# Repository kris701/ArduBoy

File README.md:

# ArduBoy

This is a project to make my own gameboy-like console, with its own scripting language and dynamic runtime on an Arduino.

Physically, its more or less equal to a Gameboy Pocket, except this one is a bit thicker and the screen is a bit smaller.
Other than that, it has the same button layout. 
Instead of using disposable batteries, it has a internal LiPo instead with a USB-C port for charging.
Games are semi-compiled into a easier to read format for the Arduino. The semi-compiled code is put on an SD card, that the ArduBoy can then parse and run.

In hindsight, it might have a bit of an overkill battery of 3000mAh, so it can technically run for a few days without a charge.

You can take a look in the [Games](./Games) folder for some already made games for the Arduino, or you can make some yourself!

You can use the CLI tool to compile the script file onto an SD card.
The tool will also do a bit of syntax checking to make sure there arent obvious errors in the script file.

## ArduBoy Script (`.abs`) Syntax

Generally the syntax of the ArduBoy Scripts are heavy encapsulation with `(` and `)`.
An example of this can be seen below:

```
(
	(:name Example)
	(:includes (:include core))

	(:func Setup
		(
			// Setup code goes here
			// This code only runs once
		)
	)

	(:func Loop
		(
			// Looping code goes here
			// The code in here will loop
		)
	)
)
```

## Parts

Here is a general list of the electronic parts that was used in this project.

* [3000 mAh battery](https://www.ebay.com/itm/121823784057)
* [USB-C Charging board](https://www.ebay.com/itm/325273541405)
* [SD card reader](https://www.ebay.com/itm/170895501953)
* [Arduino Nano](https://www.ebay.com/itm/364546971433?var=634055018693)
* [Button PCB](https://www.ebay.com/itm/296243650365?var=594299882127)
* [OLED Screen](https://www.ebay.com/itm/225810919466)
* [3.7v to 5v boster](https://www.ebay.com/itm/255301455926)

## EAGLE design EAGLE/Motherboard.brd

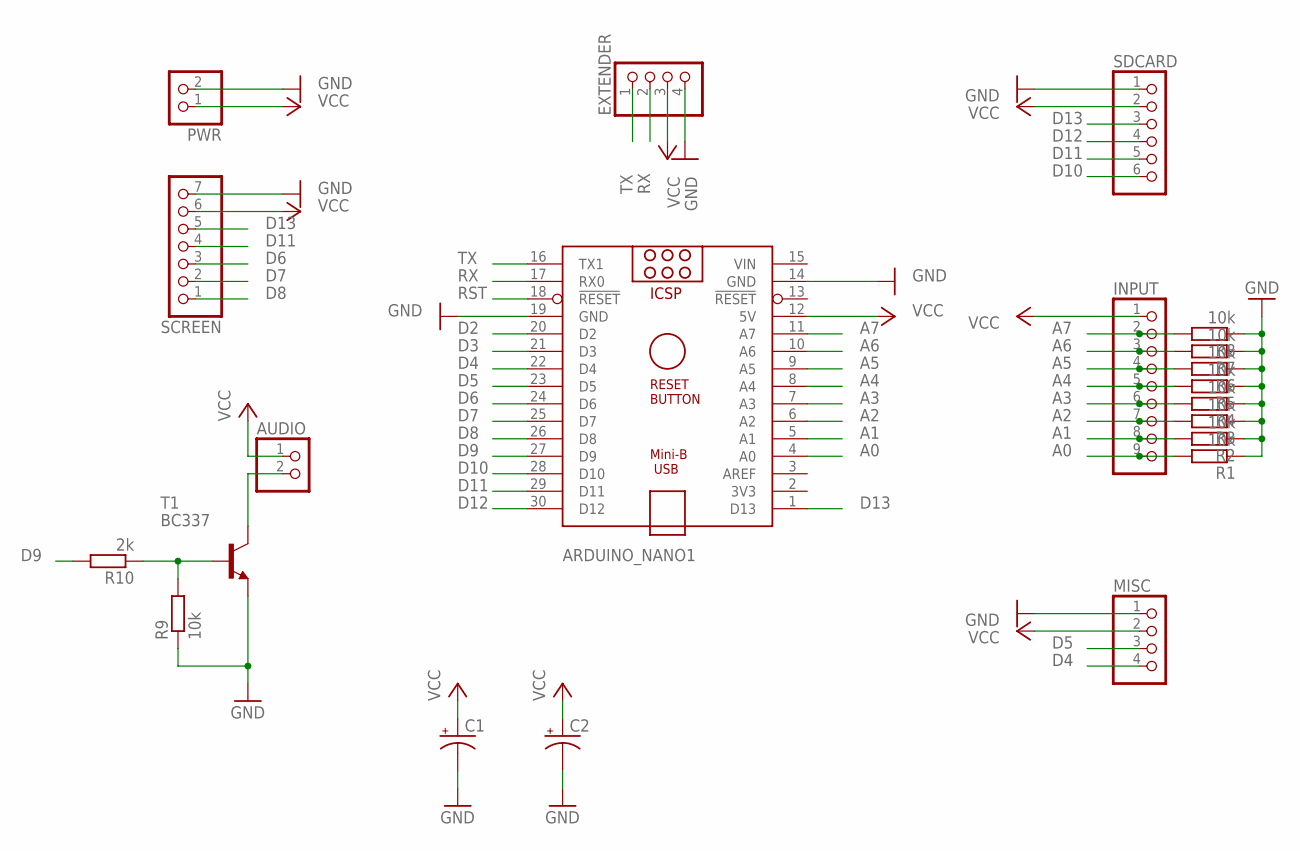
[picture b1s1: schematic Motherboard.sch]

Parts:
ARDUINO_NANO1: ARDUINO_NANO
AUDIO: PINHD-1X2; 1X02
C1, C2: CPOL-USE2.5-6; E2,5-6
EXTENDER: PINHD-1X4; 1X04
INPUT: PINHD-1X9; 1X09
MISC: PINHD-1X4; 1X04
PWR: PINHD-1X2; 1X02
R1, R2, R3, R4, R5, R6, R7, R8, R9: 10k; 0204/7
R10: 2k; 0204/7
SCREEN: PINHD-1X7; 1X07
SDCARD: PINHD-1X6; 1X06
T1: BC337; TO92

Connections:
A0: ARDUINO_NANO1.4 (A0), INPUT.9, R1.2
A1: ARDUINO_NANO1.5 (A1), INPUT.8, R2.2
A2: ARDUINO_NANO1.6 (A2), INPUT.7, R3.2
A3: ARDUINO_NANO1.7 (A3), INPUT.6, R4.2
A4: ARDUINO_NANO1.8 (A4), INPUT.5, R5.2
A5: ARDUINO_NANO1.9 (A5), INPUT.4, R6.2
A6: ARDUINO_NANO1.10 (A6), INPUT.3, R7.2
A7: ARDUINO_NANO1.11 (A7), INPUT.2, R8.2
D2: ARDUINO_NANO1.20 (D2)
D3: ARDUINO_NANO1.21 (D3)
D4: ARDUINO_NANO1.22 (D4), MISC.4
D5: ARDUINO_NANO1.23 (D5), MISC.3
D6: ARDUINO_NANO1.24 (D6), SCREEN.3
D7: ARDUINO_NANO1.25 (D7), SCREEN.2
D8: ARDUINO_NANO1.26 (D8), SCREEN.1
D9: ARDUINO_NANO1.27 (D9), R10.2
D10: ARDUINO_NANO1.28 (D10), SDCARD.6
D11: ARDUINO_NANO1.29 (D11), SCREEN.4, SDCARD.5
D12: ARDUINO_NANO1.30 (D12), SDCARD.4
D13: ARDUINO_NANO1.1 (D13), SCREEN.5, SDCARD.3
GND: ARDUINO_NANO1.14 (GND), ARDUINO_NANO1.19 (GND), C1.-, C2.-, EXTENDER.4, MISC.1, PWR.2, R1.1, R2.1, R3.1, R4.1, R5.1, R6.1, R7.1, R8.1, R9.1, SCREEN.7, SDCARD.1, T1.1 (E)
unnamed: AUDIO.2, T1.3 (C)
unnamed: R9.2, R10.1, T1.2 (B)
RST: ARDUINO_NANO1.18 (!RESET)
RX: ARDUINO_NANO1.17 (RX0), EXTENDER.2
TX: ARDUINO_NANO1.16 (TX1), EXTENDER.1
VCC: ARDUINO_NANO1.12 (5V), AUDIO.1, C1.+, C2.+, EXTENDER.3, INPUT.1, MISC.2, PWR.1, SCREEN.6, SDCARD.2
VIN: ARDUINO_NANO1.15 (VIN)

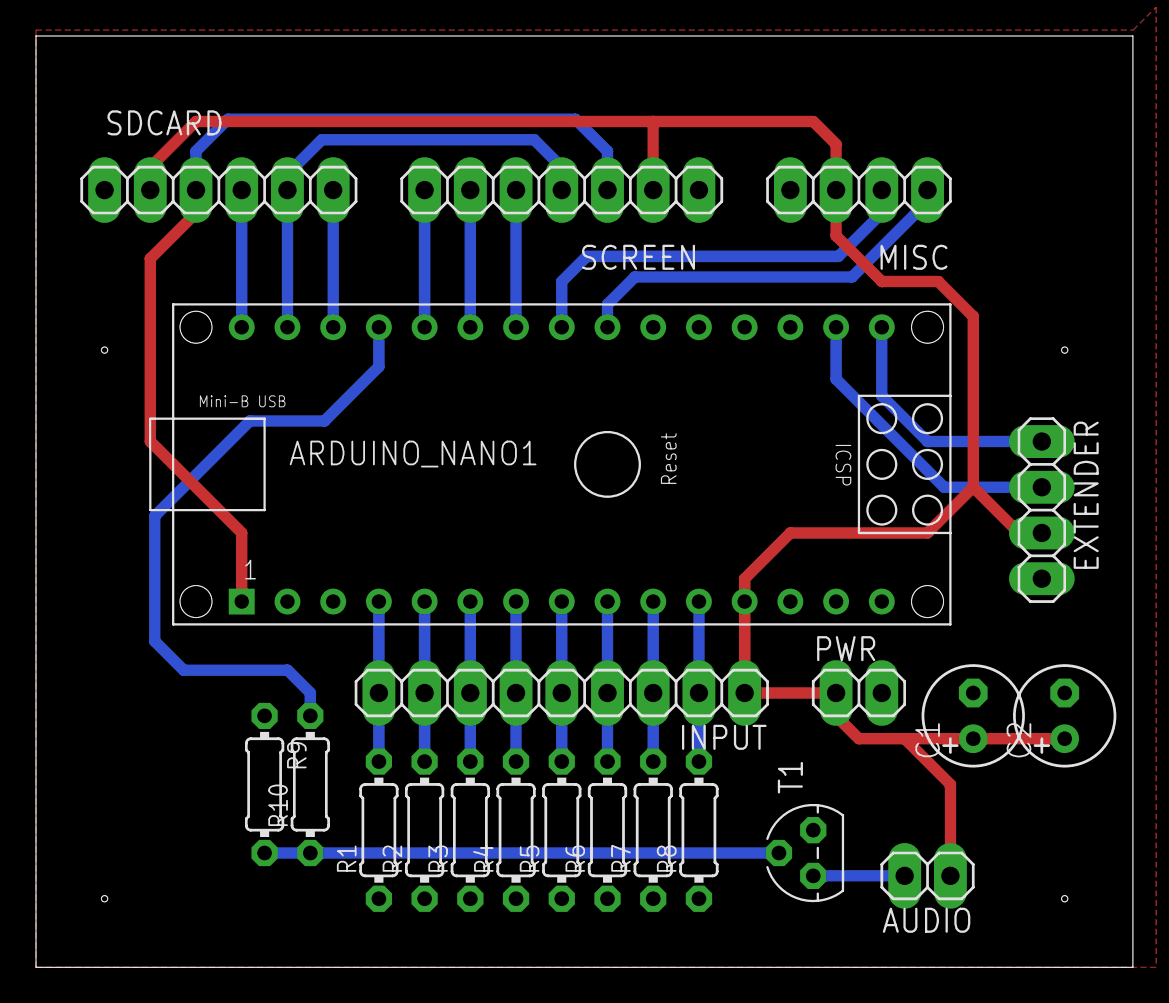
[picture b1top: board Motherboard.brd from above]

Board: 2 copper layers, 60.9 x 51.7 mm, 21 parts (0 on the bottom side), 24 nets.

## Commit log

2024-06-27 Add .gitattributes, .gitignore, README.md, and LICENSE.txt.
2024-06-27 Add project files.
2024-06-27 Initial parser logic
2024-06-27 Initial code generator setup and parser update
2024-06-27 Further extensions to the scripting language
2024-06-27 Changed the syntax to almost be PDDL-like
2024-06-27 Initial setup for the Arduino side
2024-06-28 Further additions and extensions of the simple script language
2024-06-28 * Added comments * Added external includes * Added more propper CLI controls
2024-06-30 Added variable support
2024-06-30 Added internal gotos
2024-06-30 * Renamed contextualiser to compilers * Removed unused old compiler * Added more logging * Additional check for if a script is valid
2024-06-30 Code generator update
2024-07-01 * Added mathmatical expressions (+,-,* and /) * Made so that the jmp codes are in characters instead of lines (the Arduino side needs it to be characters) * Refactoring of the initial Arduino code
2024-07-01 Fixed a bug where statics was not compiled correctly
2024-07-01 Small bugfix
2024-07-01 Added all relevant drawing methods
2024-07-01 Bytecode fixes for the opcodes
2024-07-01 Model refactoring
2024-07-01 Support for single statement branches in if, func, statics and include statements
2024-07-07 added initial EAGLE files
2024-07-08 Updated EAGLE schematics and board
2024-07-24 Updated motherboard schetch and board design
2024-07-24 Set ports correctly in the code
2024-07-24 * Redid the board design * Repinned a lot
2024-07-24 Setup for audio
2024-07-25 Added boarder drill holes to the pcb board design
2024-08-11 Got the basic arduino stuff to work
2024-08-11 Lots of fixes and optimisations
2024-08-11 Fixed the line system for if statements
2024-08-11 Opcode fix
2024-08-12 Optimisations of the runtime code
2024-08-12 Script update
2024-08-12 Typo fix
2024-08-12 Call fix
2024-08-12 Initial self test script
2024-08-12 Text expression fix
2024-08-12 Self test script fix
2024-08-12 More self test
2024-08-12 Added for loops
2024-08-12 Rect self test
2024-08-12 Rect fix
2024-08-12 Fixed bad stack pointer size
2024-08-12 Runtime bugfix
2024-08-12 Fixed a bug on the runtime, where the first value in a string was offset wrong
2024-08-14 Added a while loop
2024-08-14 Self test fix
2024-08-14 Added a parser for the while expression
2024-08-14 Large parser refactoring
2024-08-14 More refactoring
2024-08-15 * Refactoring * Split some of the compilation into a seperate optimisation step instead
2024-08-15 Added a lot more structured analysis of the scripts
2024-08-15 Added a dedicated "reserved" functions section for the script
2024-08-15 Added some more prechecks
2024-08-15 * Further code analysis * Code cleanup
2024-08-15 * Added some initial documentation * Added the current fusion design file
2024-08-17 Better exception handling
2024-08-17 Code Cleanup
2024-08-31 Input test
2024-08-31 Fix for reserved methods
2024-08-31 Core input fix
2024-08-31 Audio test and button mapping
2024-08-31 Added the modulo expression and initial snake game
2024-08-31 Snake update
2024-08-31 Fixed typo
2024-08-31 Direction fix
2024-08-31 Overflow fix
2024-08-31 Pellete logic
2024-08-31 If flip
2024-08-31 Pellete position fixing
2024-08-31 Initial position fix
2024-08-31 Higehr speed
2024-08-31 Pellete work
2024-08-31 Fixes
2024-08-31 More speed
2024-08-31 Pellete location fix
2024-09-01 * Cleanup * Better readme * Updated fusion drawing
